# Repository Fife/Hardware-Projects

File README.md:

# Hardware-Projects

Here is where my hardware projects go!

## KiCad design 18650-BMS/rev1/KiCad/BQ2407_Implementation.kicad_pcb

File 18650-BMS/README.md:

# 18650-BMS
This is a Battery Management System (BMS) for a single cell 18650 Battery for use in DIY portable audio applications. 

## Features
  -Outputs a split single supply for portable audio applications, GND, 2.5V, 5V. 
  
  -USB-C Charging port
  
  -Easily replaceable 18650 cell form factor.

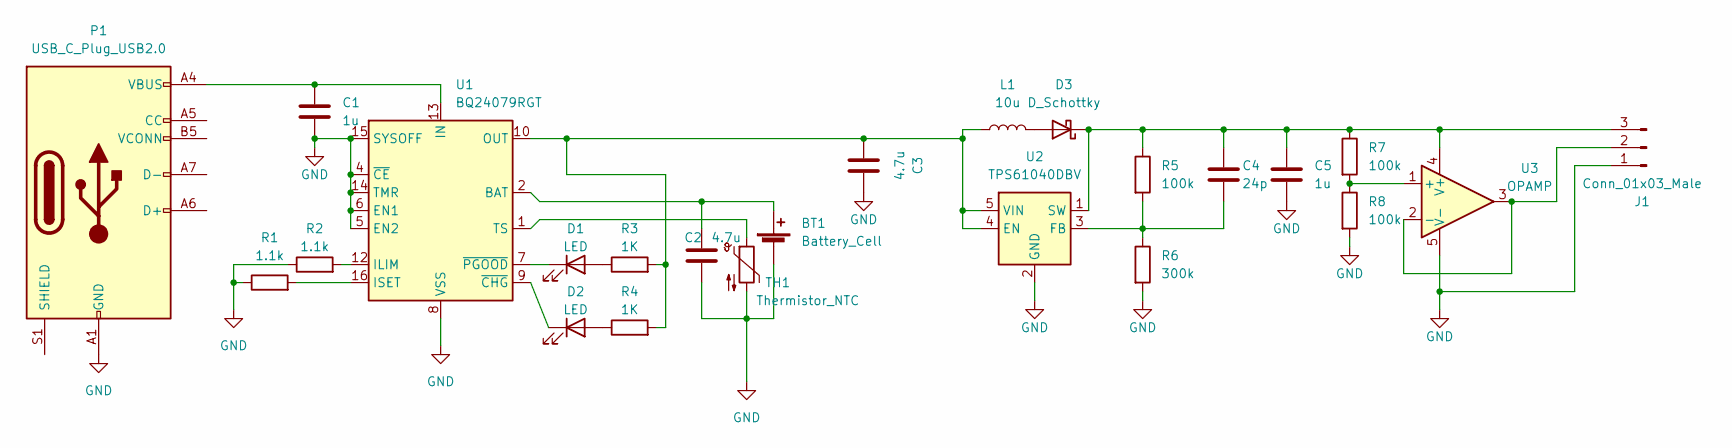
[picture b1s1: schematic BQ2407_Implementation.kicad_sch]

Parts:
BT1: Battery_Cell; BatteryHolder_Keystone_1042_1x18650
C1: 1u; C_0603_1608Metric
C2, C3: 4.7u; C_0603_1608Metric
C4: 24p; C_Disc_D5.0mm_W2.5mm_P2.50mm
C5: 1u; C_Disc_D5.0mm_W2.5mm_P5.00mm
D1, D2: LED; LED_1206_3216Metric_Pad1.42x1.75mm_HandSolder
D3: D_Schottky; D_SOD-123
J1: Conn_01x03_Male; PinHeader_1x03_P2.54mm_Vertical
L1: 10u; INDM125125X600N
P1: USB_C_Plug_USB2.0; USB_C_Receptacle_GCT_USB4085
R1, R2: 1.1k; R_0805_2012Metric
R3, R4: 1K; R_0805_2012Metric
R5, R7, R8: 100k; R_0805_2012Metric
R6: 300k; R_0805_2012Metric
TH1: Thermistor_NTC; SolderWire-0.1sqmm_1x02_P3.6mm_D0.4mm_OD1mm
U1: BQ24079RGT; VQFN-16-1EP_3x3mm_P0.5mm_EP1.6x1.6mm
U2: TPS61040DBV; SOT-23-5
U3: OPAMP; SOT95P280X145-6N

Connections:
GND: BT1.2 (-), C1.2, C2.2, C3.2, C5.2, J1.1, P1.A1 (GND), P1.A12 (GND), P1.B1 (GND), P1.B12 (GND), R1.1, R2.1, R6.2, R8.2, TH1.2, U1.4 (~CE), U1.5 (EN2), U1.6 (EN1), U1.8 (VSS), U1.14 (TMR), U1.15 (SYSOFF), U1.17 (VSS), U2.2 (GND), U3.5 (V-)
unnamed: BT1.1 (+), C2.1, U1.2 (BAT), U1.3 (BAT)
unnamed: C1.1, P1.A4 (VBUS), P1.A9 (VBUS), P1.B4 (VBUS), P1.B9 (VBUS), U1.13 (IN)
unnamed: C3.1, L1.1, R3.2, R4.2, U1.10 (OUT), U1.11 (OUT), U2.4 (EN), U2.5 (VIN)
unnamed: C4.1, C5.1, D3.1 (K), J1.3, R5.1, R7.1, U2.1 (SW), U3.4 (V+)
unnamed: C4.2, R5.2, R6.1, U2.3 (FB)
unnamed: D1.1 (K), U1.7 (~PGOOD)
unnamed: D1.2 (A), R3.1
unnamed: D2.1 (K), U1.9 (~CHG)
unnamed: D2.2 (A), R4.1
unnamed: D3.2 (A), L1.2
unnamed: J1.2, U3.2 (-), U3.3
unnamed: R1.2, U1.16 (ISET)
unnamed: R2.2, U1.12 (ILIM)
unnamed: R7.2, R8.1, U3.1 (+)
unnamed: TH1.1, U1.1 (TS)

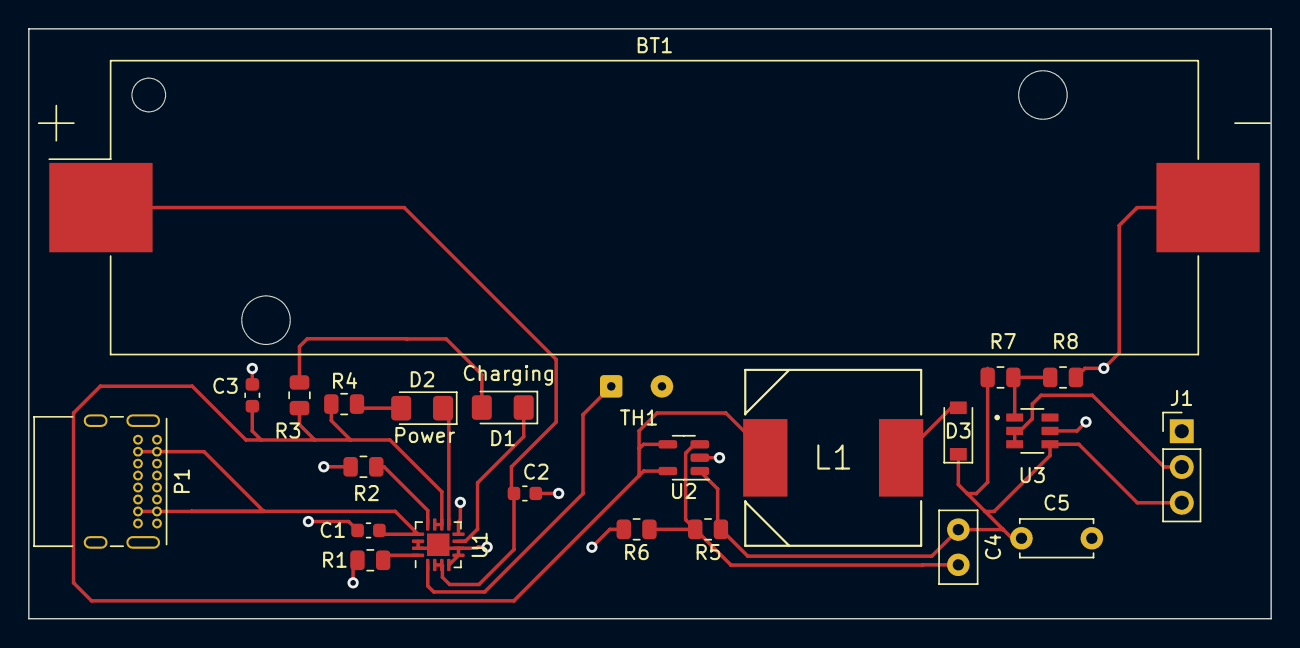
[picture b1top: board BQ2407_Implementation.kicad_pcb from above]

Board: 2 copper layers, 88.3 x 41.9 mm, 24 parts (0 on the bottom side), 16 nets.

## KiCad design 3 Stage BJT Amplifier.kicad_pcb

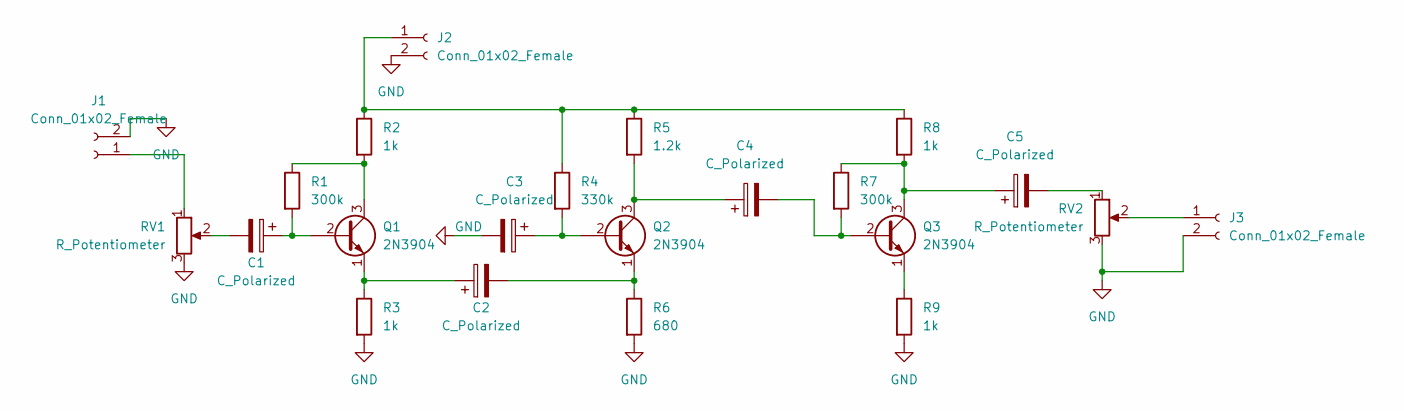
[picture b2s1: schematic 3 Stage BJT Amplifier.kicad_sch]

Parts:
C1, C2, C3, C4, C5: C_Polarized; C_Radial_D5.0mm_H11.0mm_P2.00mm
J1, J2, J3: Conn_01x02_Female; SolderWire-0.1sqmm_1x02_P3.6mm_D0.4mm_OD1mm
Q1, Q2, Q3: 2N3904; TO-92_Inline
R1, R7: 300k; R_Axial_DIN0204_L3.6mm_D1.6mm_P5.08mm_Horizontal
R2, R3, R8, R9: 1k; R_Axial_DIN0204_L3.6mm_D1.6mm_P5.08mm_Horizontal
R4: 330k; R_Axial_DIN0204_L3.6mm_D1.6mm_P5.08mm_Horizontal
R5: 1.2k; R_Axial_DIN0204_L3.6mm_D1.6mm_P5.08mm_Horizontal
R6: 680; R_Axial_DIN0204_L3.6mm_D1.6mm_P5.08mm_Horizontal
RV1, RV2: R_Potentiometer; SolderWire-0.1sqmm_1x03_P3.6mm_D0.4mm_OD1mm

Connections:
GND: C3.2, J1.2, J2.2, J3.2, R3.2, R6.2, R9.2, RV1.3, RV2.3
unnamed: C1.1, Q1.2 (B), R1.2
unnamed: C1.2, RV1.2
unnamed: C2.1, Q1.1 (E), R3.1
unnamed: C2.2, Q2.1 (E), R6.1
unnamed: C3.1, Q2.2 (B), R4.2
unnamed: C4.1, Q2.3 (C), R5.2
unnamed: C4.2, Q3.2 (B), R7.2
unnamed: C5.1, Q3.3 (C), R7.1, R8.2
unnamed: C5.2, RV2.1
unnamed: J1.1, RV1.1
unnamed: J2.1, R2.1, R4.1, R5.1, R8.1
unnamed: J3.1, RV2.2
unnamed: Q1.3 (C), R1.1, R2.2
unnamed: Q3.1 (E), R9.1

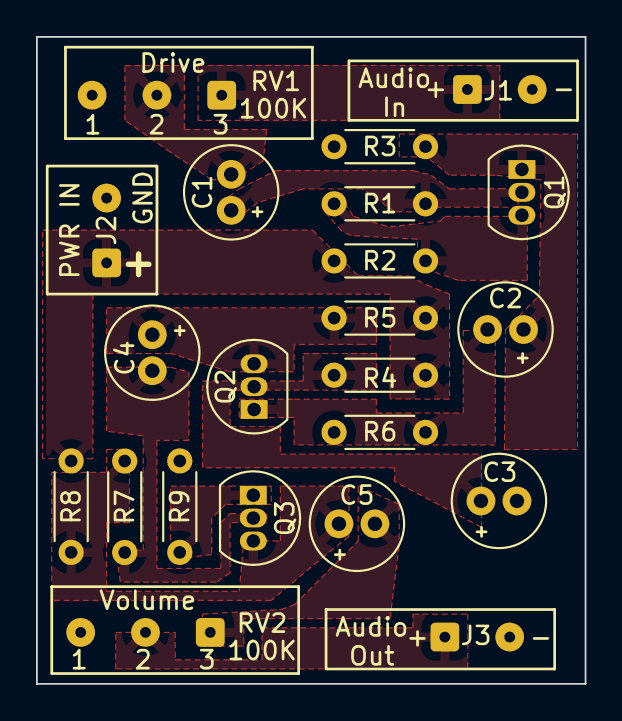
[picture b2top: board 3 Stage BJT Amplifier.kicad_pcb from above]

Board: 2 copper layers, 30.5 x 35.9 mm, 22 parts (0 on the bottom side), 15 nets.

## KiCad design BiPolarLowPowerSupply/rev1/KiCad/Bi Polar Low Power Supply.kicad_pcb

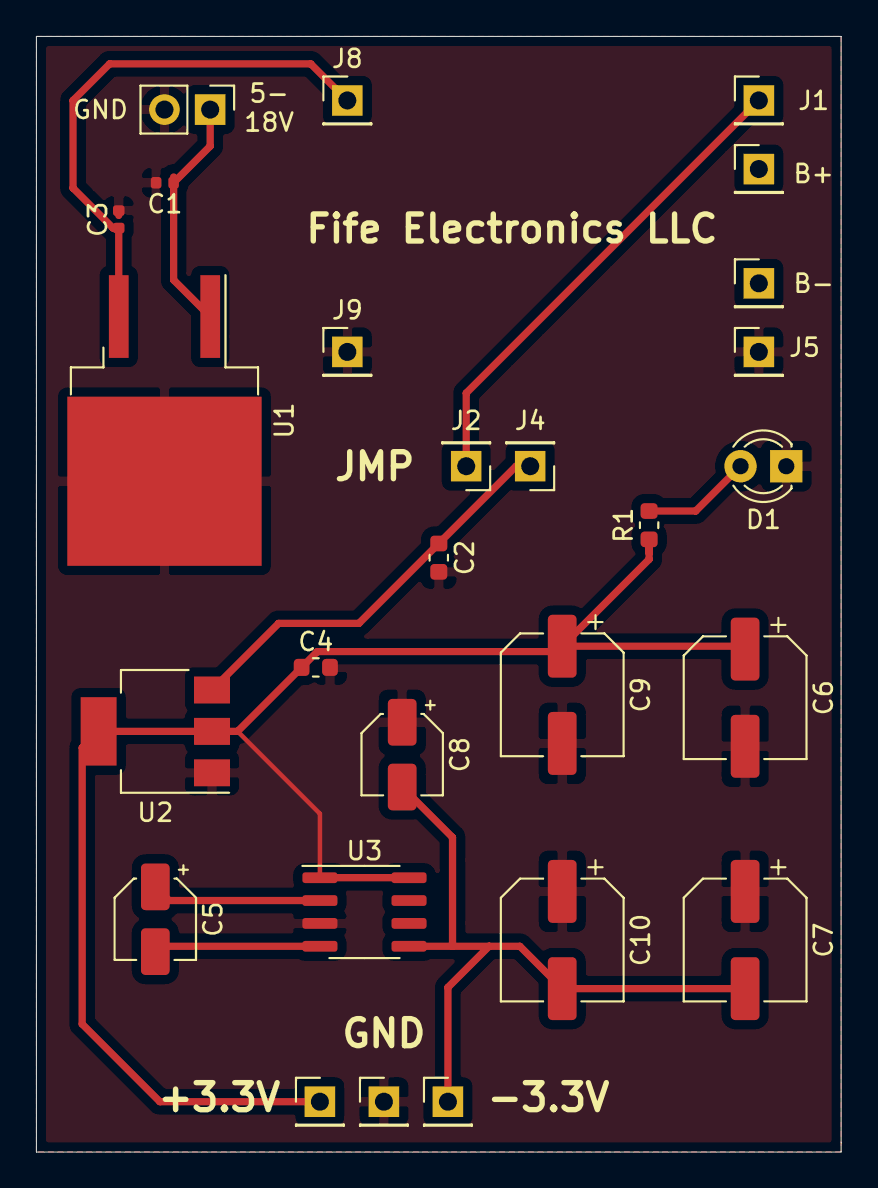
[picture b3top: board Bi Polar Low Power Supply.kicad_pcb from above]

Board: 2 copper layers, 44.7 x 62.0 mm, 27 parts (0 on the bottom side), 10 nets.

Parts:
C1, C3: 0.1uF; C_0402_1005Metric
C2: 100nF; C_0603_1608Metric
C4: 10uF; C_0603_1608Metric
C5, C8: 10uF; CP_Elec_4x5.7
C6, C7, C9, C10: 100uF; CP_Elec_6.3x7.7
D1: LED; LED_D3.0mm_FlatTop
J1, J2: 3.7V FROM CHARGER; PinHeader_1x01_P2.54mm_Vertical
J3: 9V-18V Input; PinHeader_1x02_P2.54mm_Vertical
J4: 3.7V INTO REG; PinHeader_1x01_P2.54mm_Vertical
J5: 0V FROM CHARGER; PinHeader_1x01_P2.54mm_Vertical
J6: BATT+; PinHeader_1x01_P2.54mm_Vertical
J7: BATT -; PinHeader_1x01_P2.54mm_Vertical
J8: 5V Out to Charger; PinHeader_1x01_P2.54mm_Vertical
J9: 0V Out to charger; PinHeader_1x01_P2.54mm_Vertical
J10: +3.3V; PinHeader_1x01_P2.54mm_Vertical
J11: 0V GND; PinHeader_1x01_P2.54mm_Vertical
J12: -3.3V; PinHeader_1x01_P2.54mm_Vertical
R1: 1k; R_0603_1608Metric
U1: L7805; TO-263-2
U2: LD1117S33TR_SOT223; SOT-223-3_TabPin2
U3: MAX1044; SOIC-8_3.9x4.9mm_P1.27mm

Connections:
GND: C1.2, C2.2, C3.2, C4.2, C6.2, C7.1, C8.1, C9.2, C10.1, D1.1, J3.2, J5.1, J9.1, J11.1, U1.2, U2.1, U3.3
unnamed: C1.1, J3.1, U1.1
unnamed: C2.1, J4.1, U2.3
unnamed: C3.1, J8.1, U1.3
unnamed: C4.1, C6.1, C9.1, J10.1, R1.1, U2.2, U3.1, U3.8
unnamed: C5.1, U3.2
unnamed: C5.2, U3.4
unnamed: C7.2, C8.2, C10.2, J12.1, U3.5
unnamed: D1.2, R1.2
unnamed: J1.1, J2.1

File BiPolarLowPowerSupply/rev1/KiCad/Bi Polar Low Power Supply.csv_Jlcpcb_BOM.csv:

Comment,Designator,Footprint,LCSC Part #
0.1uF,C1,C_0402_1005Metric,JLCPcbRef
3.7V INTO REG,J4,PinHeader_1x01_P2.54mm_Vertical,JLCpcbRef
3.7V FROM CHARGER,J2,PinHeader_1x01_P2.54mm_Vertical,JLCpcbRef
BATT -,J7,PinHeader_1x01_P2.54mm_Vertical,JLCpcbRef
BATT+,J6,PinHeader_1x01_P2.54mm_Vertical,JLCpcbRef
0.1uF,C3,C_0402_1005Metric,JLCpcbRef
5V Out to Charger,J8,PinHeader_1x01_P2.54mm_Vertical,JLCpcbRef
0V FROM CHARGER,J5,PinHeader_1x01_P2.54mm_Vertical,JLCpcbRef
3.7V FROM CHARGER,J1,PinHeader_1x01_P2.54mm_Vertical,JLCpcbRef
0V Out to charger,J9,PinHeader_1x01_P2.54mm_Vertical,JLCpcbRef
LED,D1,LED_D3.0mm_FlatTop,JLCpcbRef
1k,R1,R_0603_1608Metric,JLCpcbRef
0V GND,J11,PinHeader_1x01_P2.54mm_Vertical,JLCpcbRef
9V-18V Input,J3,PinHeader_1x02_P2.54mm_Vertical,JLCpcbRef
-3.3V,J12,PinHeader_1x01_P2.54mm_Vertical,JLCpcbRef
+3.3V,J10,PinHeader_1x01_P2.54mm_Vertical,JLCpcbRef
10uF,C5,CP_Elec_4x5.7,JLCpcbRef
MAX1044,U3,SOIC-8_3.9x4.9mm_P1.27mm,JLCpcbRef
100uF,C7,CP_Elec_6.3x7.7,JLCpcbRef
100uF,C6,CP_Elec_6.3x7.7,JLCpcbRef
100uF,C10,CP_Elec_6.3x7.7,JLCpcbRef
100uF,C9,CP_Elec_6.3x7.7,JLCpcbRef
LD1117S33TR_SOT223,U2,SOT-223-3_TabPin2,JLCpcbRef
10uF,C4,C_0603_1608Metric,JLCpcbRef
100nF,C2,C_0603_1608Metric,JLCpcbRef
10uF,C8,CP_Elec_4x5.7,JLCpcbRef
L7805,U1,TO-263-2,JLCpcbRef

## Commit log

2022-06-26 Rename 18650-BMS/KiCad/temp.md to 18650-BMS/rev1/KiCad/temp.md
2022-06-26 Rename 18650-BMS/rev1/KiCad/BQ2407_Implementation.kicad_pcb to 18650-BMS/rev1/BQ2407_Implementation.kicad_pcb
2022-06-26 Rename 18650-BMS/rev1/KiCad/BQ2407_Implementation.kicad_prl to 18650-BMS/rev1/BQ2407_Implementation.kicad_prl
2022-06-26 Rename 18650-BMS/rev1/KiCad/BQ2407_Implementation.kicad_pro to 18650-BMS/rev1/BQ2407_Implementation.kicad_pro
2022-06-26 Rename 18650-BMS/rev1/KiCad/BQ2407_Implementation.kicad_sch to 18650-BMS/rev1/BQ2407_Implementation.kicad_sch
2022-06-26 Rename BiPolarLowPowerSupply/rev1/KiCad/Bi Polar Low Power Supply.kicad_pcb to BiPolarLowPowerSupply/rev1/Bi Polar Low Power Supply.kicad_pcb
2022-06-26 Rename BiPolarLowPowerSupply/rev1/KiCad/Bi Polar Low Power Supply.pro to BiPolarLowPowerSupply/rev1/Bi Polar Low Power Supply.pro
2022-06-26 Rename BiPolarLowPowerSupply/rev1/KiCad/Bi Polar Low Power Supply.sch to BiPolarLowPowerSupply/rev1/Bi Polar Low Power Supply.sch
2022-06-29 Rename 3 Stage BJT Amplifier.kicad_pcb to Multistage-Amplifier-BJT/3 Stage BJT Amplifier.kicad_pcb
2022-06-29 Rename 3 Stage BJT Amplifier.kicad_pro to Multistage-Amplifier-BJT/3 Stage BJT Amplifier.kicad_pro
2022-06-29 Rename 3 Stage BJT Amplifier.kicad_sch to Multistage-Amplifier-BJT/3 Stage BJT Amplifier.kicad_sch
